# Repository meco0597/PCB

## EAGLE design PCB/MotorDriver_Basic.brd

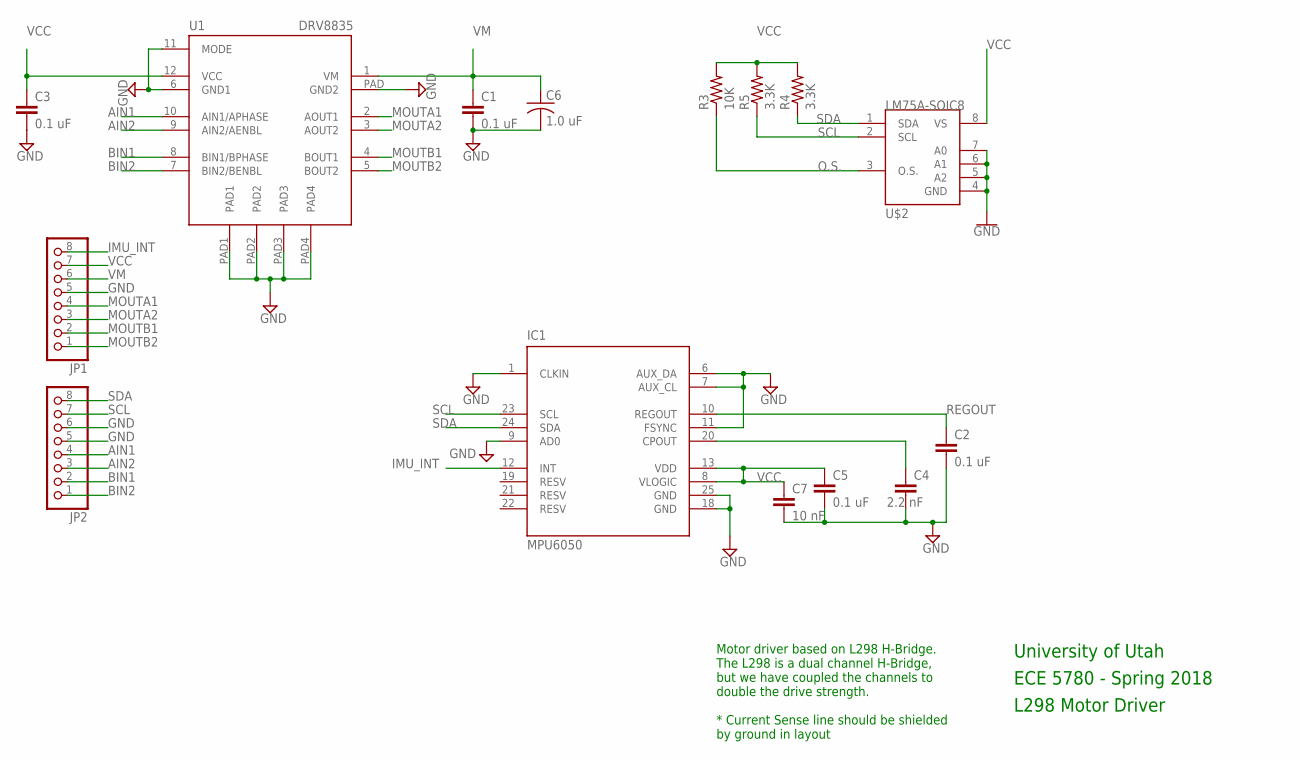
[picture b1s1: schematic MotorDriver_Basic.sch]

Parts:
C1, C2, C3, C5: 0.1 uF; C1206
C4: 2.2 nF; C1206
C6: 1.0 uF; C025-050X050
C7: 10 nF; C1206
IC1: MPU6050; QFN50P400X400X95-25T265X275N
JP1, JP2: PINHD-1X8; 1X08
R3: 10K; M1206
R4, R5: 3.3K; M1206
U1: DRV8835; WSON_2X3
U$2: LM75A-SOIC8; SOIC-8

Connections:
AIN1: JP2.4, U1.10 (AIN1/APHASE)
AIN2: JP2.3, U1.9 (AIN2/AENBL)
BIN1: JP2.2, U1.8 (BIN1/BPHASE)
BIN2: JP2.1, U1.7 (BIN2/BENBL)
GND: C1.2, C2.2, C3.2, C4.2, C5.2, C6.2, C7.2, IC1.1 (CLKIN), IC1.6 (AUX_DA), IC1.7 (AUX_CL), IC1.9 (AD0), IC1.11 (FSYNC), IC1.18 (GND), IC1.25 (GND), JP1.5, JP2.5, JP2.6, U1.6 (GND1), U1.11 (MODE), U1.PAD (GND2), U1.PAD1, U1.PAD2, U1.PAD3, U1.PAD4, U$2.4 (GND), U$2.5 (A2), U$2.6 (A1), U$2.7 (A0)
IMU_INT: IC1.12 (INT), JP1.8
MOUTA1: JP1.4, U1.2 (AOUT1)
MOUTA2: JP1.3, U1.3 (AOUT2)
MOUTB1: JP1.2, U1.4 (BOUT1)
MOUTB2: JP1.1, U1.5 (BOUT2)
unnamed: C4.1, IC1.20 (CPOUT)
O.S.: R3.1, U$2.3 (O.S.)
REGOUT: C2.1, IC1.10 (REGOUT)
SCL: IC1.23 (SCL), JP2.7, R5.1, U$2.2 (SCL)
SDA: IC1.24 (SDA), JP2.8, R4.1, U$2.1 (SDA)
VCC: C3.1, C5.1, C7.1, IC1.8 (VLOGIC), IC1.13 (VDD), JP1.7, R3.2, R4.2, R5.2, U1.12 (VCC), U$2.8 (VS)
VM: C1.1, C6.1, JP1.6, U1.1 (VM)

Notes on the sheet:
University of Utah
ECE 5780 - Spring 2018
L298 Motor Driver
Motor driver based on L298 H-Bridge. The L298 is a dual channel H-Bridge, but we have coupled the channels to double the drive strength. * Current Sense line should be shielded by ground in layout

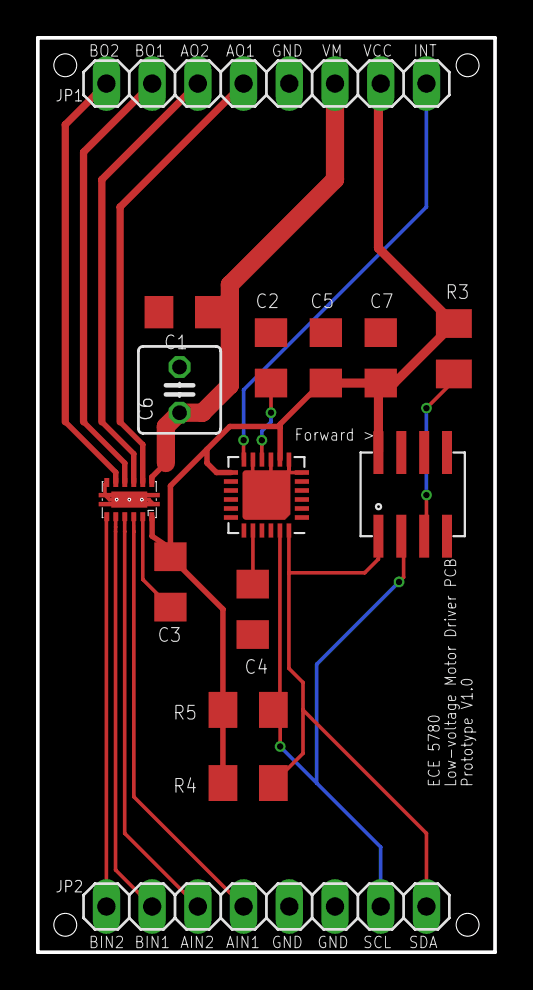
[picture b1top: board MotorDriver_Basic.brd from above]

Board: 2 copper layers, 25.4 x 50.8 mm, 15 parts (0 on the bottom side), 17 nets.

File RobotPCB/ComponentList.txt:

All resistors, capacitors, and LEDs use the 1206 package.

Preliminary Component List:
1x DRV8835 low-voltage motor driver
1x JST 2 Pin SMT RA connector
1x MPU 6050 IMU
1x SMT USB Mini-B connector
1x MCP73831/2 LiPo battery charger
1x TLV757P LDO
1x ESP-12-F 
1x CP2104-F03-GM
6x 10k Ohm 
3x 1k Ohm 
1x 4.7k Ohm 
1x 2k Ohm 
2x 3.3k Ohm 
1x 1 uF electrolytic capacitor (through hole)
5x 0.1 uF ceramic capacitor 
3x 1 uF ceramic capacitor 
3x 10 uF ceramic capacitor 
1x 2.2 nF ceramic capacitor 
1x 10 nF ceramic capacitor 
2x LEDs
1x PNP transistor Package: SOT23
1x NPN transistor Package: SOT23
1x MBR120HW diode Package: SOD123
2x 8 Pin Header

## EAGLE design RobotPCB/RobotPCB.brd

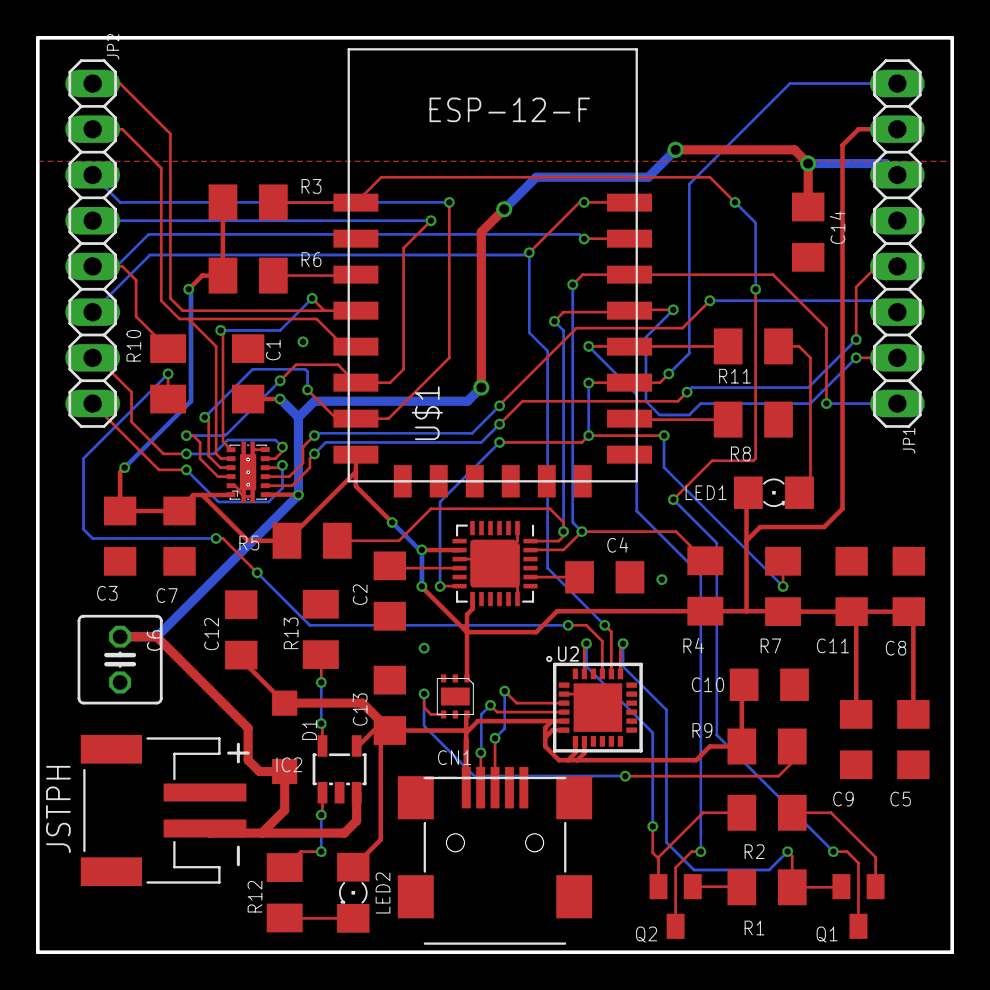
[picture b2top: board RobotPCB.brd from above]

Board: 2 copper layers, 50.8 x 50.8 mm, 42 parts (0 on the bottom side), 35 nets.

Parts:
C1, C2, C3, C5, C8: 0.1 uF; C1206
C4: 2.2 nF; C1206
C6: 1.0 uF; C025-050X050
C7: 10 nF; C1206
C9, C13, C14: 10 uF; C1206
C10, C11, C12: 1 uF; C1206
CN1: USB-MINIB
D1: MBR120HW; SOD123
IC1: MPU6050; QFN50P400X400X95-25T265X275N
IC2: MCP73831/OT; SOT23-5L
JP1, JP2: 1X08
JSTPH: JST-PH-2-SMT-RA
LED1, LED2: 1206
Q1, Q2: SOT23
R1: 10ki; M1206
R2, R3, R6, R7, R9: 10k; M1206
R4, R5: 3.3K; M1206
R8: 4.7k; M1206
R10, R11, R12: 1k; M1206
R13: 2k; M1206
U1: DRV8835; WSON_2X3
U2: CP2104-F03-GM; QFN-24-4X4
U$1: ESP8266_ESP-12; ESP8266-ESP12
U$2: TLV757P; WSON-6

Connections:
DTR: Q2.2, R2.2, U2.23
EN: R6.1, U$1.3
GND: C1.2, C2.2, C3.2, C4.2, C5.2, C6.2, C7.2, C8.2, C9.2, C10.2, C11.2, C12.2, C13.2, C14.2, CN1.GND, IC1.1, IC1.9, IC1.11, IC1.18, IC1.25, IC2.2, JP1.5, JSTPH.1, R8.1, R13.2, U1.6, U1.11, U1.PAD, U1.PAD1, U1.PAD2, U1.PAD3, U1.PAD4, U2.2, U2.PAD, U$1.15, U$2.3, U$2.7
GPIO0: Q2.3, R11.2, U$1.18
GPIO2: IC1.12, JP1.8, R7.2, U$1.17
GPIO4: IC1.24, JP1.2, R5.1, U$1.19
GPIO5: IC1.23, JP1.1, R4.1, U$1.20
GPIO12: JP2.4, U1.10, U$1.6
GPIO13: JP2.3, U1.9, U$1.7
GPIO14: JP2.2, U1.8, U$1.5
GPIO16: JP2.1, U1.7, U$1.4
MOUTA1: JP1.4, U1.2
MOUTA2: JP1.3, U1.3
MOUTB1: JP2.8, U1.4
MOUTB2: JP2.7, U1.5
unnamed: C4.1, IC1.20
unnamed: Q1.1, R2.1
unnamed: R9.2, U$2.4
unnamed: CN1.D+, U2.3
unnamed: Q2.1, R1.1
unnamed: CN1.D-, U2.4
unnamed: LED1.C, R11.1
unnamed: IC2.5, R13.1
unnamed: IC2.1, R12.2
unnamed: LED2.C, R12.1
unnamed: R8.2, U$1.16
REGOUT: C2.1, IC1.10
RESET: Q1.3, R3.1, U$1.1
RTS: Q1.2, R1.2, U2.19
RXD: JP2.5, R10.2, U$1.21
TXD: JP2.6, U2.20, U$1.22
USB_RX: R10.1, U2.21
VBAT: C1.1, C6.1, C14.1, D1.A, IC2.3, JP1.6, JSTPH.2, U1.1
VBUS: C10.1, C12.1, C13.1, CN1.VBUS, D1.C, IC2.4, LED2.A, R9.1, U2.5, U2.6, U2.7, U2.8, U$2.6
VCC: C3.1, C5.1, C7.1, C8.1, C9.1, C11.1, IC1.8, IC1.13, JP1.7, LED1.A, R3.2, R4.2, R5.2, R6.2, R7.1, U1.12, U$1.8, U$2.1

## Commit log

2019-03-28 add lbr file
2019-03-28 new lbr file
2019-03-28 added the motor driver to schematic.
2019-03-28 add imu footprint lib
2019-03-28 Finished the Schematic.
2019-03-29 Finished the board file.
2019-03-29 Tweaked the board file
2019-03-30 Added some connections
2019-03-30 Tweaked schematic/Created board
2019-04-17 Fixed the fucking asshole's mistake where the fuck did we get that fucking foot print fuck fuck fuck fuck fuck
2019-04-25 Lil Fix
2019-04-28 Added full robot PCB with ESP-12-F
2019-04-28 Added component list
2019-06-04 Added text to pins
2019-06-04 Fixed ESP-12S module

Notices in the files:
parts and their libraries:
SparkFun-PowerSymbols: Licensing: Creative Commons ShareAlike 4.0 International - https://creativecommons.org/licenses/by-sa/4.0
